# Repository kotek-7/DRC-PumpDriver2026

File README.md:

キャチロボ2026で使う、6chポンプドライバです。  
KiCad ↓
https://kicanvas.org/?repo=https%3A%2F%2Fgithub.com%2Fkotek-7%2FDRC-PumpDriver2026

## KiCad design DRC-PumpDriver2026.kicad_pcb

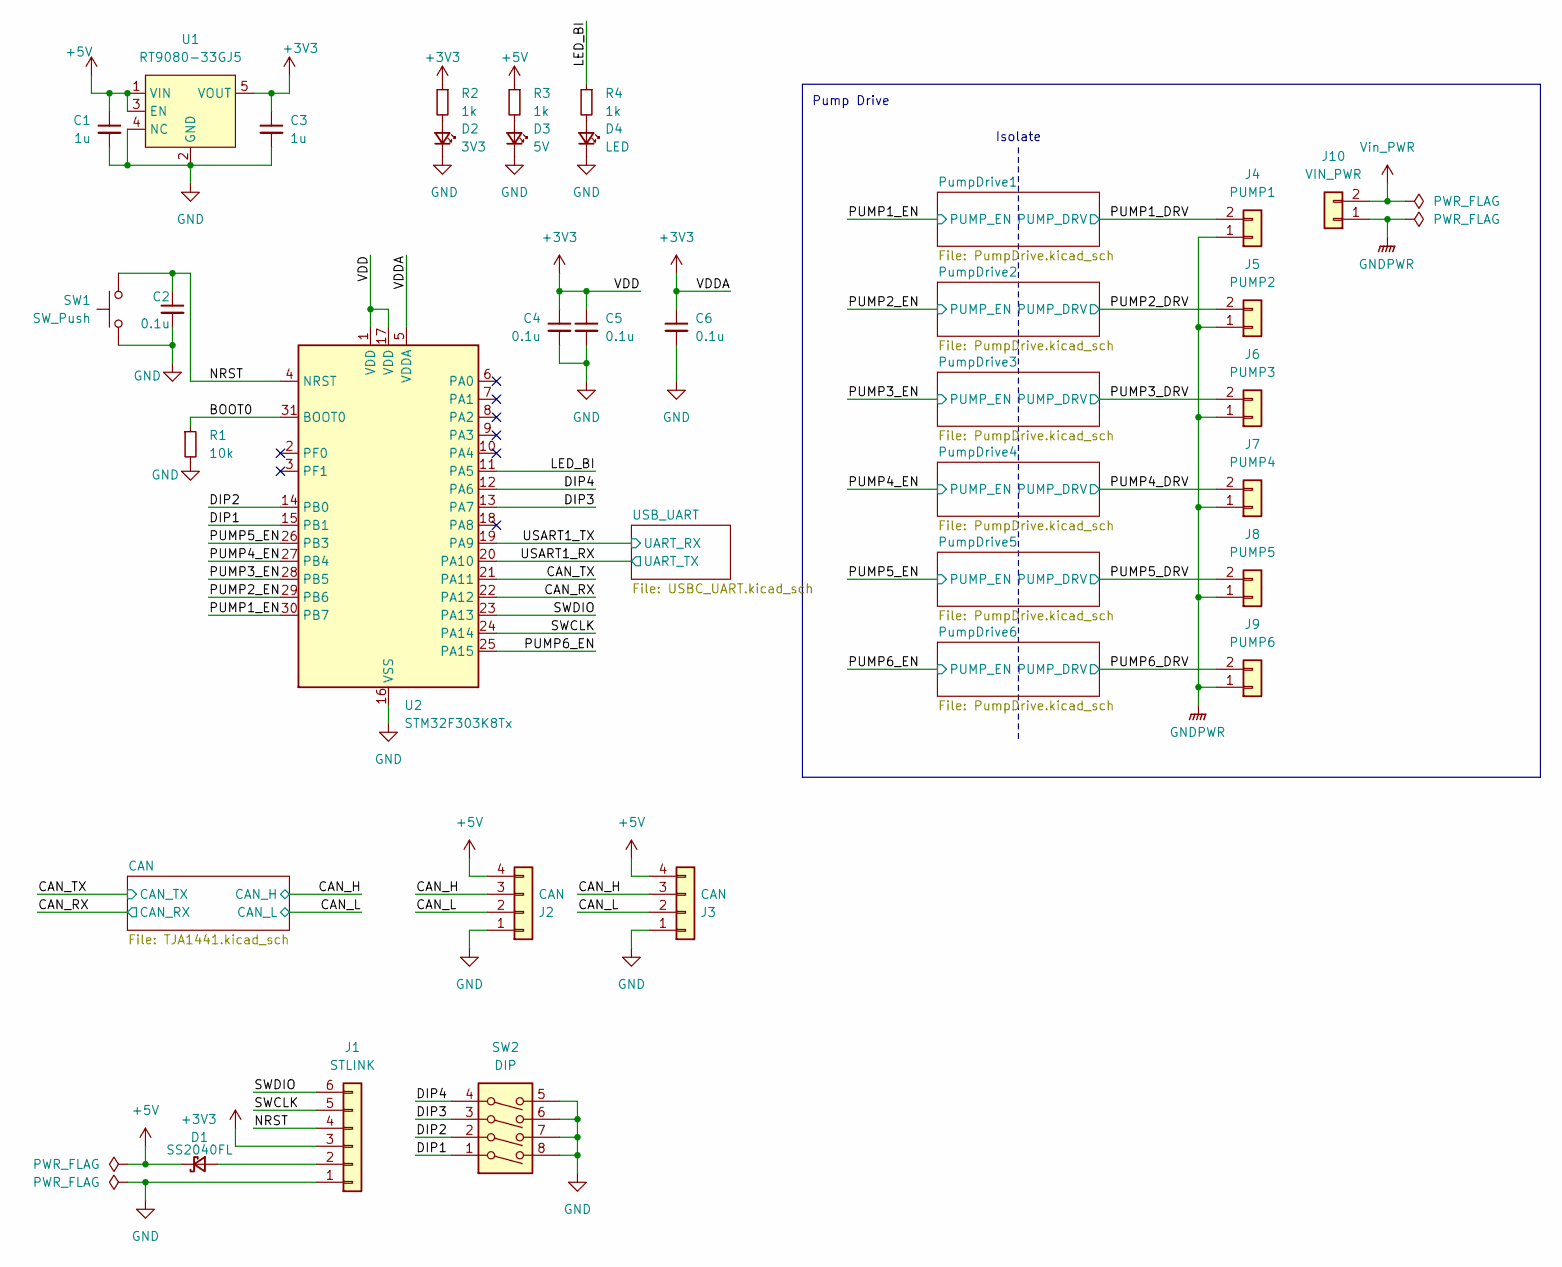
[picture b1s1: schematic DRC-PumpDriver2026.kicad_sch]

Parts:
C1, C3: 1u; C_0805_2012Metric_Pad1.18x1.45mm_HandSolder
C2, C4, C5, C6: 0.1u; C_0603_1608Metric_Pad1.08x0.95mm_HandSolder
D1: SS2040FL; D_SOD-123F
D2: 3V3; LED_0603_1608Metric_Pad1.05x0.95mm_HandSolder
D3: 5V; LED_0603_1608Metric_Pad1.05x0.95mm_HandSolder
D4: LED; LED_0603_1608Metric_Pad1.05x0.95mm_HandSolder
J1: STLINK; IDC-Header_2x03_P2.54mm_Vertical
J2, J3: CAN; JST_XH_S4B-XH-A_1x04_P2.50mm_Horizontal; LCSC x
J4: PUMP1; JST_XH_B2B-XH-A_1x02_P2.50mm_Vertical
J5: PUMP2; JST_XH_B2B-XH-A_1x02_P2.50mm_Vertical
J6: PUMP3; JST_XH_B2B-XH-A_1x02_P2.50mm_Vertical
J7: PUMP4; JST_XH_B2B-XH-A_1x02_P2.50mm_Vertical
J8: PUMP5; JST_XH_B2B-XH-A_1x02_P2.50mm_Vertical
J9: PUMP6; JST_XH_B2B-XH-A_1x02_P2.50mm_Vertical
J10: VIN_PWR; AMASS_XT30PW-M_1x02_P2.50mm_Horizontal
R1: 10k; R_0603_1608Metric_Pad0.98x0.95mm_HandSolder
R2, R3, R4: 1k; R_0603_1608Metric_Pad0.98x0.95mm_HandSolder
SW1: SW_Push; SW_SPST_EVQPE1
SW2: DIP; SW_DIP_SPSTx04_Slide_Copal_CHS-04B_W7.62mm_P1.27mm
U1: RT9080-33GJ5; TSOT-23-5
U2: STM32F303K8Tx; LQFP-32_7x7mm_P0.8mm

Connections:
+3V3: C3.1, C4.1, C5.1, C6.1, J1.3, R2.1, U1.5 (VOUT), U2.1 (VDD), U2.5 (VDDA), U2.17 (VDD); also elsewhere on the board
+5V: C1.1, D1.1 (K), J2.4, J3.4, R3.1, U1.1 (VIN), U1.3 (EN); also elsewhere on the board
/BOOT0: R1.1, U2.31 (BOOT0)
/CAN_H: J2.3, J3.3; also elsewhere on the board
/CAN_L: J2.2, J3.2; also elsewhere on the board
/CAN_RX: U2.22 (PA12); also elsewhere on the board
/CAN_TX: U2.21 (PA11); also elsewhere on the board
/DIP1: SW2.1, U2.15 (PB1)
/DIP2: SW2.2, U2.14 (PB0)
/DIP3: SW2.3, U2.13 (PA7)
/DIP4: SW2.4, U2.12 (PA6)
/LED_BI: R4.1, U2.11 (PA5)
/NRST: C2.1, J1.4, SW1.1, U2.4 (NRST)
/PUMP1_DRV: J4.2; also elsewhere on the board
/PUMP1_EN: U2.30 (PB7); also elsewhere on the board
/PUMP2_DRV: J5.2; also elsewhere on the board
/PUMP2_EN: U2.29 (PB6); also elsewhere on the board
/PUMP3_DRV: J6.2; also elsewhere on the board
/PUMP3_EN: U2.28 (PB5); also elsewhere on the board
/PUMP4_DRV: J7.2; also elsewhere on the board
/PUMP4_EN: U2.27 (PB4); also elsewhere on the board
/PUMP5_DRV: J8.2; also elsewhere on the board
/PUMP5_EN: U2.26 (PB3); also elsewhere on the board
/PUMP6_DRV: J9.2; also elsewhere on the board
/PUMP6_EN: U2.25 (PA15); also elsewhere on the board
/SWCLK: J1.5, U2.24 (PA14)
/SWDIO: J1.6, U2.23 (PA13)
/USART1_RX: U2.20 (PA10); also elsewhere on the board
/USART1_TX: U2.19 (PA9); also elsewhere on the board
GND: C1.2, C2.2, C3.2, C4.2, C5.2, C6.2, D2.1 (K), D3.1 (K), D4.1 (K), J1.1, J2.1, J3.1, R1.2, SW1.2, SW2.5, SW2.6, SW2.7, SW2.8, U1.2 (GND), U1.4 (NC), U2.16 (VSS), U2.32 (VSS); also elsewhere on the board
GNDPWR: J4.1, J5.1, J6.1, J7.1, J8.1, J9.1, J10.1
unnamed: D1.2 (A), J1.2
unnamed: D2.2 (A), R2.2
unnamed: D3.2 (A), R3.2
unnamed: D4.2 (A), R4.2
Vin_PWR: J10.2; also elsewhere on the board

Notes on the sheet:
Pump Drive
Isolate

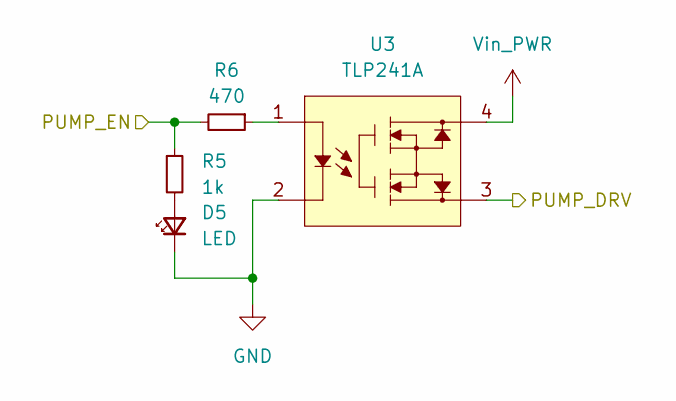
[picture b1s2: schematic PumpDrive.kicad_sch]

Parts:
D5: LED; LED_0603_1608Metric_Pad1.05x0.95mm_HandSolder
R5: 1k; R_0603_1608Metric_Pad0.98x0.95mm_HandSolder
R6: 470; R_0603_1608Metric_Pad0.98x0.95mm_HandSolder
U3: TLP241A; DIP4_TOS

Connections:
/PUMP1_DRV: U3.3; also elsewhere on the board
/PUMP1_EN: R5.1, R6.2; also elsewhere on the board
GND: D5.1 (K), U3.2; also elsewhere on the board
unnamed: D5.2 (A), R5.2
unnamed: R6.1, U3.1
Vin_PWR: U3.4; also elsewhere on the board

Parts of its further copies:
D6, D7, D8, D9, D10: LED; LED_0603_1608Metric_Pad1.05x0.95mm_HandSolder
R7, R9, R11, R13, R15: 1k; R_0603_1608Metric_Pad0.98x0.95mm_HandSolder
R8, R10, R12, R14, R16: 470; R_0603_1608Metric_Pad0.98x0.95mm_HandSolder
U4, U5, U6, U7, U8: TLP241A; DIP4_TOS

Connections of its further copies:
/PUMP2_DRV: U4.3; also elsewhere on the board
/PUMP2_EN: R7.1, R8.2; also elsewhere on the board
/PUMP3_DRV: U5.3; also elsewhere on the board
/PUMP3_EN: R9.1, R10.2; also elsewhere on the board
/PUMP4_DRV: U6.3; also elsewhere on the board
/PUMP4_EN: R11.1, R12.2; also elsewhere on the board
/PUMP5_DRV: U7.3; also elsewhere on the board
/PUMP5_EN: R13.1, R14.2; also elsewhere on the board
/PUMP6_DRV: U8.3; also elsewhere on the board
/PUMP6_EN: R15.1, R16.2; also elsewhere on the board
GND: D6.1 (K), D7.1 (K), D8.1 (K), D9.1 (K), D10.1 (K), U4.2, U5.2, U6.2, U7.2, U8.2; also elsewhere on the board
unnamed: D6.2 (A), R7.2
unnamed: D7.2 (A), R9.2
unnamed: D8.2 (A), R11.2
unnamed: D9.2 (A), R13.2
unnamed: D10.2 (A), R15.2
unnamed: R8.1, U4.1
unnamed: R10.1, U5.1
unnamed: R12.1, U6.1
unnamed: R14.1, U7.1
unnamed: R16.1, U8.1
Vin_PWR: U4.4, U5.4, U6.4, U7.4, U8.4; also elsewhere on the board

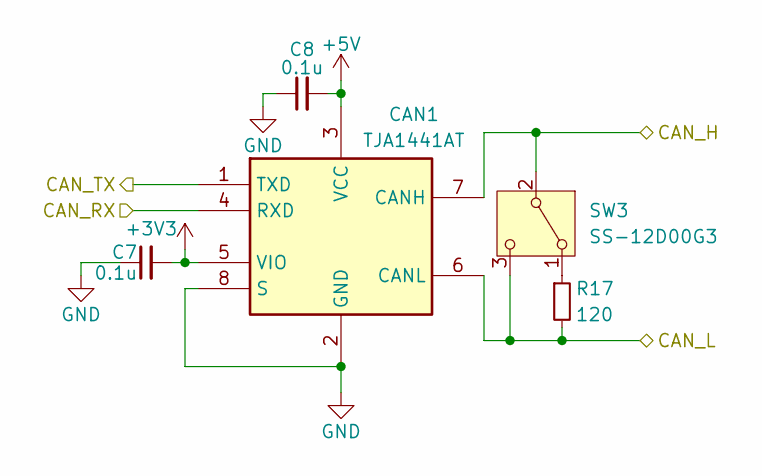
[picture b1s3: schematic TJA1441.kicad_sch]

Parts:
C7, C8: 0.1u; C_0603_1608Metric_Pad1.08x0.95mm_HandSolder
CAN1: TJA1441AT; SOIC127P600X175-8N; Manufacturer_Part_Number TJA1441AT
R17: 120; R_0603_1608Metric_Pad0.98x0.95mm_HandSolder
SW3: SS-12D00G3

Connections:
+3V3: C7.2, CAN1.5 (VIO); also elsewhere on the board
+5V: C8.2, CAN1.3 (VCC); also elsewhere on the board
/CAN_H: CAN1.7 (CANH), SW3.2 (B); also elsewhere on the board
/CAN_L: CAN1.6 (CANL), R17.2, SW3.3 (C); also elsewhere on the board
/CAN_RX: CAN1.4 (RXD); also elsewhere on the board
/CAN_TX: CAN1.1 (TXD); also elsewhere on the board
GND: C7.1, C8.1, CAN1.2 (GND), CAN1.8 (S); also elsewhere on the board
unnamed: R17.1, SW3.1 (A)

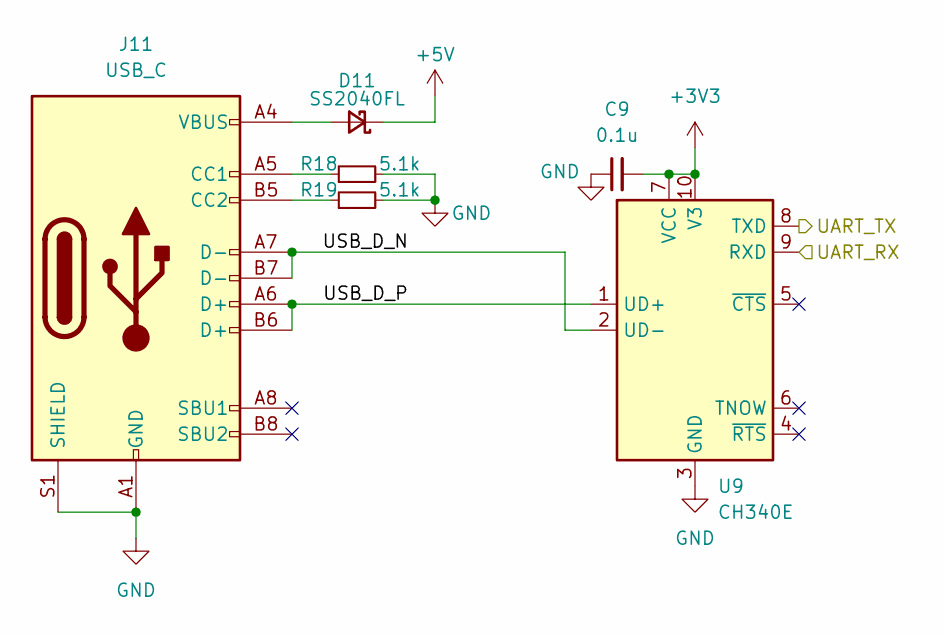
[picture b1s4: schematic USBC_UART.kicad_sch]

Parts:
C9: 0.1u; C_0603_1608Metric_Pad1.08x0.95mm_HandSolder
D11: SS2040FL; D_SOD-123F
J11: USB_C; USB_C_Receptacle_GCT_USB4105-xx-A_16P_TopMnt_Horizontal
R18, R19: 5.1k; R_0603_1608Metric_Pad0.98x0.95mm_HandSolder
U9: CH340E; MSOP-10_3x3mm_P0.5mm

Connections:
+3V3: C9.2, U9.7 (VCC), U9.10 (V3); also elsewhere on the board
+5V: D11.1 (K); also elsewhere on the board
/USART1_RX: U9.8 (TXD); also elsewhere on the board
/USART1_TX: U9.9 (RXD); also elsewhere on the board
/USB_UART/USB_D_N: J11.A7 (D-), J11.B7 (D-), U9.2 (UD-)
/USB_UART/USB_D_P: J11.A6 (D+), J11.B6 (D+), U9.1 (UD+)
GND: C9.1, J11.A1 (GND), J11.A12 (GND), J11.B1 (GND), J11.B12 (GND), J11.S1 (SHIELD), R18.2, R19.2, U9.3 (GND); also elsewhere on the board
unnamed: D11.2 (A), J11.A4 (VBUS), J11.A9 (VBUS), J11.B4 (VBUS), J11.B9 (VBUS)
unnamed: J11.A5 (CC1), R18.1
unnamed: J11.B5 (CC2), R19.1

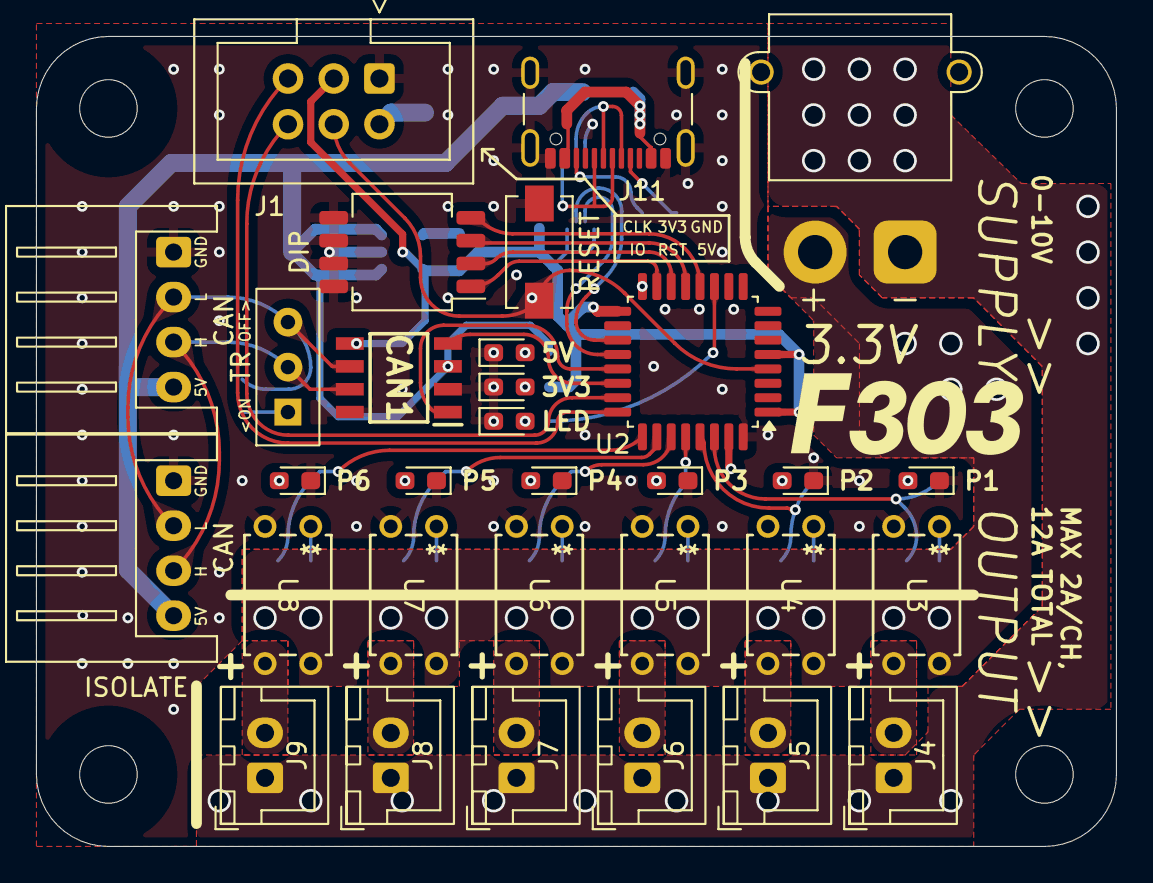
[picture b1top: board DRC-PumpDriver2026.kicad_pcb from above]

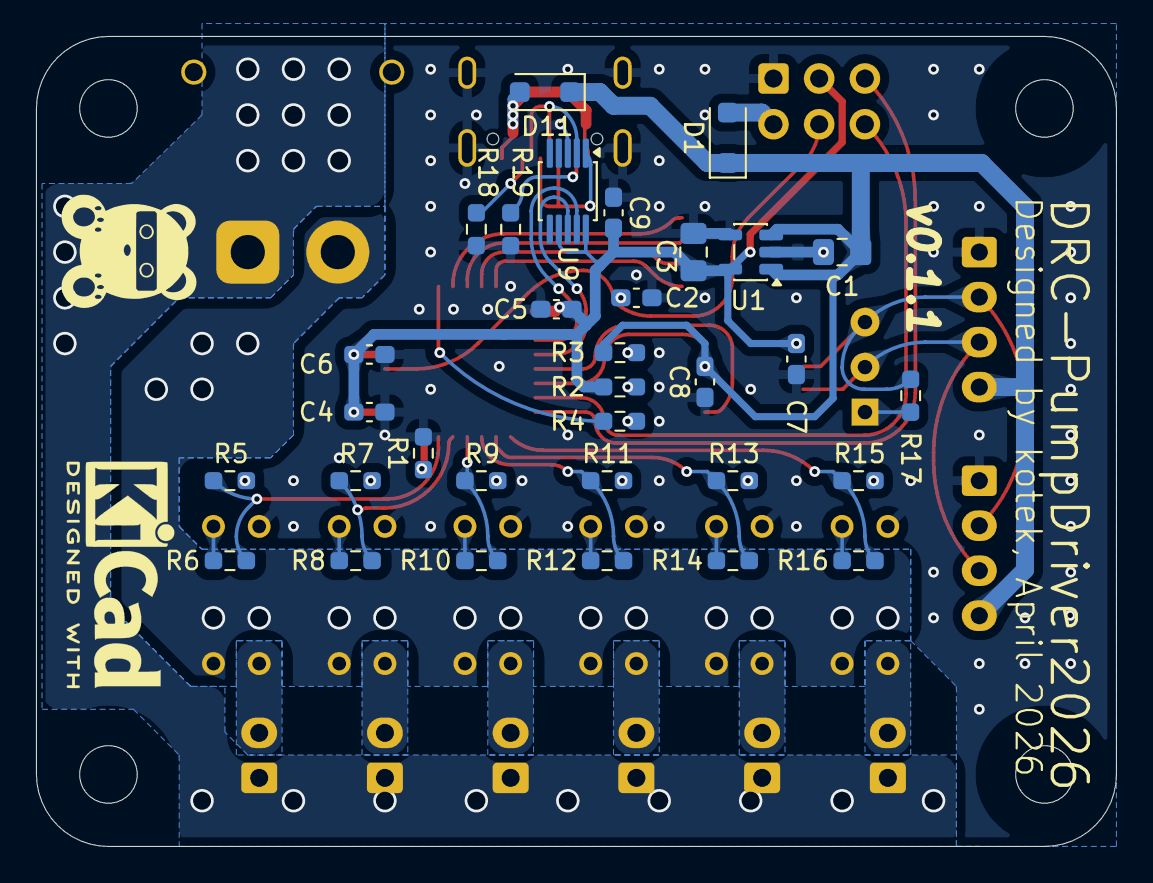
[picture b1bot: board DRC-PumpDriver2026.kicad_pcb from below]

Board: 2 copper layers, 60.0 x 45.0 mm, 63 parts (32 on the bottom side), 54 nets.

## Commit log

2026-04-01 シルクスクリーンと被らないようにビアを調整
2026-04-01 シルクスクリーンのフォントを変更
2026-04-01 シルクスクリーンを修正
2026-04-01 抜けてたフォトカプラの抵抗を追加
2026-04-02 ロボクマのシルクスクリーンの位置を変更
2026-04-03 KiCad v10 に対応
2026-04-04 謎の変更
2026-04-04 gitignore を変更
2026-04-05 Revert "KiCad v10 に対応"
    This reverts commit 3aa1e3521e1af97ba20d861f86dccbc91a936ced.
2026-04-05 バージョン表記を追加
2026-04-07 DCDCを外して、電源入力に変更、v0.0.2
2026-04-17 CubeMXプロジェクトを追加
2026-04-18 STLINK書込みをボックスヘッダへ、USB追加、v0.1.0
2026-04-19 README を変更
2026-04-25 レギュレータのフットプリントを修正
2026-05-02 v0.1.1
